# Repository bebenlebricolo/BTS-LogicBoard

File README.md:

# BTS-LogicBoard
Beer thermoregulation system logic board.
This board is meant to provide a PWM control signal to the [BTS-MainBoard-Control](https://github.com/bebenlebricolo/BTS-MainBoard-Control) board and is driven by an external "enable" signal, which is a signal coming from an external pump driver (at least in the first revisions).

This board is envisioned as a starting point as it only embeds generic electronic devices, meaning no code at all.
I've done this on purpose, to keep things relatively simple and eliminating the need to iterate over software revisions, bug fixes, etc.
As the functionalities implemented by this board are relatively simple, I thought it would be a nice alternative to go only with a NE555 (the famous one) and few other electronic components such as comparators and logic gates to perform the basic functions.

# Features
This boards boats the following features :
* 1 MHz (or so) PWM signal with linear (...or so) duty cycle control
* Cooling fan automatic turn on when board is enabled and turn off after a precalculated delay (around 120s) when the board is disabled
* Externaly driven : the PWM signal only starts up when an input signal is applied on the enable pins. This is meant to receive a pump driver signal in order to start up
* Mechanical interface (switches and potentiometer) with status leds
  * Power on status LED
  * PWM enabled status LED
  * PWM intensity status LED

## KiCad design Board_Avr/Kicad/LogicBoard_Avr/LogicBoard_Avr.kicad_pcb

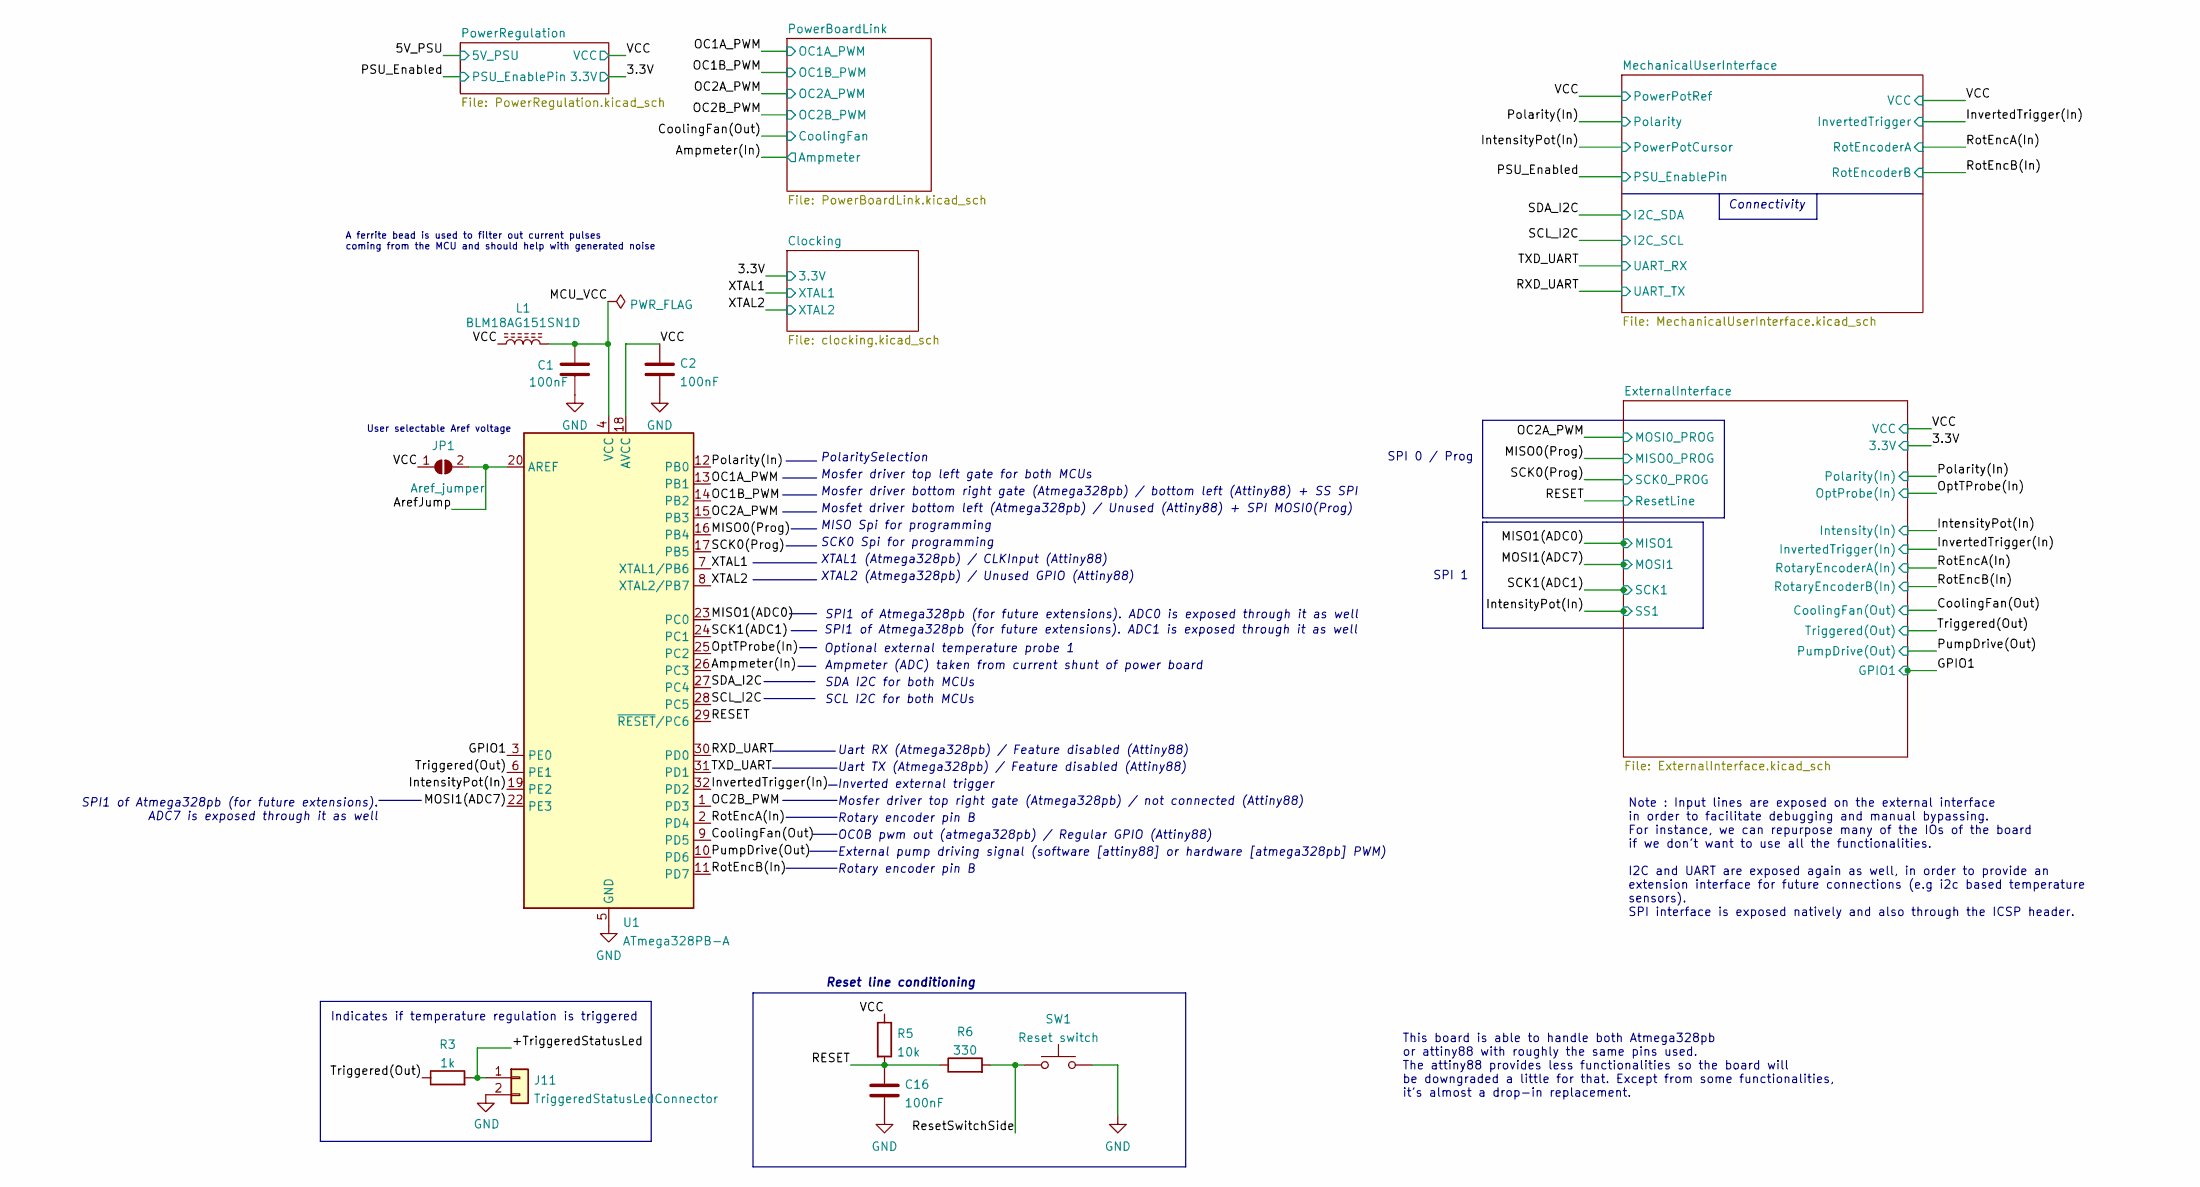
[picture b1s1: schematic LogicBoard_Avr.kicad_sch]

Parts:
C1, C2, C16: 100nF; C_1206_3216Metric
J11: TriggeredStatusLedConnector; PinHeader_1x02_P2.54mm_Vertical
JP1: Aref_jumper; SolderJumper-2_P1.3mm_Open_RoundedPad1.0x1.5mm
L1: BLM18AG151SN1D; L_0603_1608Metric
R3: 1k; R_1206_3216Metric_Pad1.30x1.75mm_HandSolder
R5: 10k; R_1206_3216Metric_Pad1.30x1.75mm_HandSolder
R6: 330; R_1206_3216Metric_Pad1.30x1.75mm_HandSolder
SW1: Reset switch; SW_PUSH_6mm_H4.3mm
U1: ATmega328PB-A; TQFP-32_7x7mm_P0.8mm

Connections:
/+TriggeredStatusLed: J11.1, R3.2
/Ampmeter(In): U1.26 (PC3); also elsewhere on the board
/ArefJump: JP1.2 (B), U1.20 (AREF)
/CoolingFan(Out): U1.9 (PD5); also elsewhere on the board
/GPIO1: U1.3 (PE0); also elsewhere on the board
/IntensityPot(In): U1.19 (PE2); also elsewhere on the board
/InvertedTrigger(In): U1.32 (PD2); also elsewhere on the board
/MCU_VCC: C1.1, L1.2, U1.4 (VCC)
/MISO0(Prog): U1.16 (PB4); also elsewhere on the board
/MISO1(ADC0): U1.23 (PC0); also elsewhere on the board
/MOSI1(ADC7): U1.22 (PE3); also elsewhere on the board
/OC1A_PWM: U1.13 (PB1); also elsewhere on the board
/OC1B_PWM: U1.14 (PB2); also elsewhere on the board
/OC2A_PWM: U1.15 (PB3); also elsewhere on the board
/OC2B_PWM: U1.1 (PD3); also elsewhere on the board
/OptTProbe(In): U1.25 (PC2); also elsewhere on the board
/Polarity(In): U1.12 (PB0); also elsewhere on the board
/PumpDrive(Out): U1.10 (PD6); also elsewhere on the board
/RESET: C16.1, R5.2, R6.1, U1.29 (~RESET/PC6); also elsewhere on the board
/RXD_UART: U1.30 (PD0); also elsewhere on the board
/ResetSwitchSide: R6.2, SW1.1
/RotEncA(In): U1.2 (PD4); also elsewhere on the board
/RotEncB(In): U1.11 (PD7); also elsewhere on the board
/SCK0(Prog): U1.17 (PB5); also elsewhere on the board
/SCK1(ADC1): U1.24 (PC1); also elsewhere on the board
/SCL_I2C: U1.28 (PC5); also elsewhere on the board
/SDA_I2C: U1.27 (PC4); also elsewhere on the board
/TXD_UART: U1.31 (PD1); also elsewhere on the board
/Triggered(Out): R3.1, U1.6 (PE1); also elsewhere on the board
/VCC: C2.1, JP1.1 (A), L1.1, R5.1, U1.18 (AVCC); also elsewhere on the board
/XTAL1: U1.7 (XTAL1/PB6); also elsewhere on the board
/XTAL2: U1.8 (XTAL2/PB7)
GND: C1.2, C2.2, C16.2, J11.2, SW1.2, U1.5 (GND), U1.21 (GND); also elsewhere on the board

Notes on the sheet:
SPI1 of Atmega328pb (for future extensions). ADC7 is exposed through it as well
Rotary encoder pin B
PolaritySelection
User selectable Aref voltage
OC0B pwm out (atmega328pb) / Regular GPIO (Attiny88)
Note : Input lines are exposed on the external interface in order to facilitate debugging and manual bypassing. For instance, we can repurpose many of the IOs of the board if we don't want to use all the functionalities. I2C and UART are exposed again as well, in order to provide an extension inter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
SPI 1
SPI1 of Atmega328pb (for future extensions). ADC1 is exposed through it as well
This board is able to handle both Atmega328pb or attiny88 with roughly the same pins used. The attiny88 provides less functionalities so the board will be downgraded a little for that. Except from some functionalities, it's almost a drop-in replacement.
XTAL2 (Atmega328pb) / Unused GPIO (Attiny88)
Mosfet driver bottom left (Atmega328pb) / Unused (Attiny88) + SPI MOSI0(Prog)
Reset line conditioning
SPI1 of Atmega328pb (for future extensions). ADC0 is exposed through it as well
Inverted external trigger
Connectivity
SDA I2C for both MCUs
MISO Spi for programming
External pump driving signal (software [attiny88] or hardware [atmega328pb] PWM)
Uart TX (Atmega328pb) / Feature disabled (Attiny88)
Mosfer driver bottom right gate (Atmega328pb) / bottom left (Attiny88) + SS SPI
Mosfer driver top left gate for both MCUs
Mosfer driver top right gate (Atmega328pb) / not connected (Attiny88)
XTAL1 (Atmega328pb) / CLKInput (Attiny88)
Ampmeter (ADC) taken from current shunt of power board
SCK0 Spi for programming
Optional external temperature probe 1
Indicates if temperature regulation is triggered
SPI 0 / Prog
Uart RX (Atmega328pb) / Feature disabled (Attiny88)
SCL I2C for both MCUs
A ferrite bead is used to filter out current pulses coming from the MCU and should help with generated noise

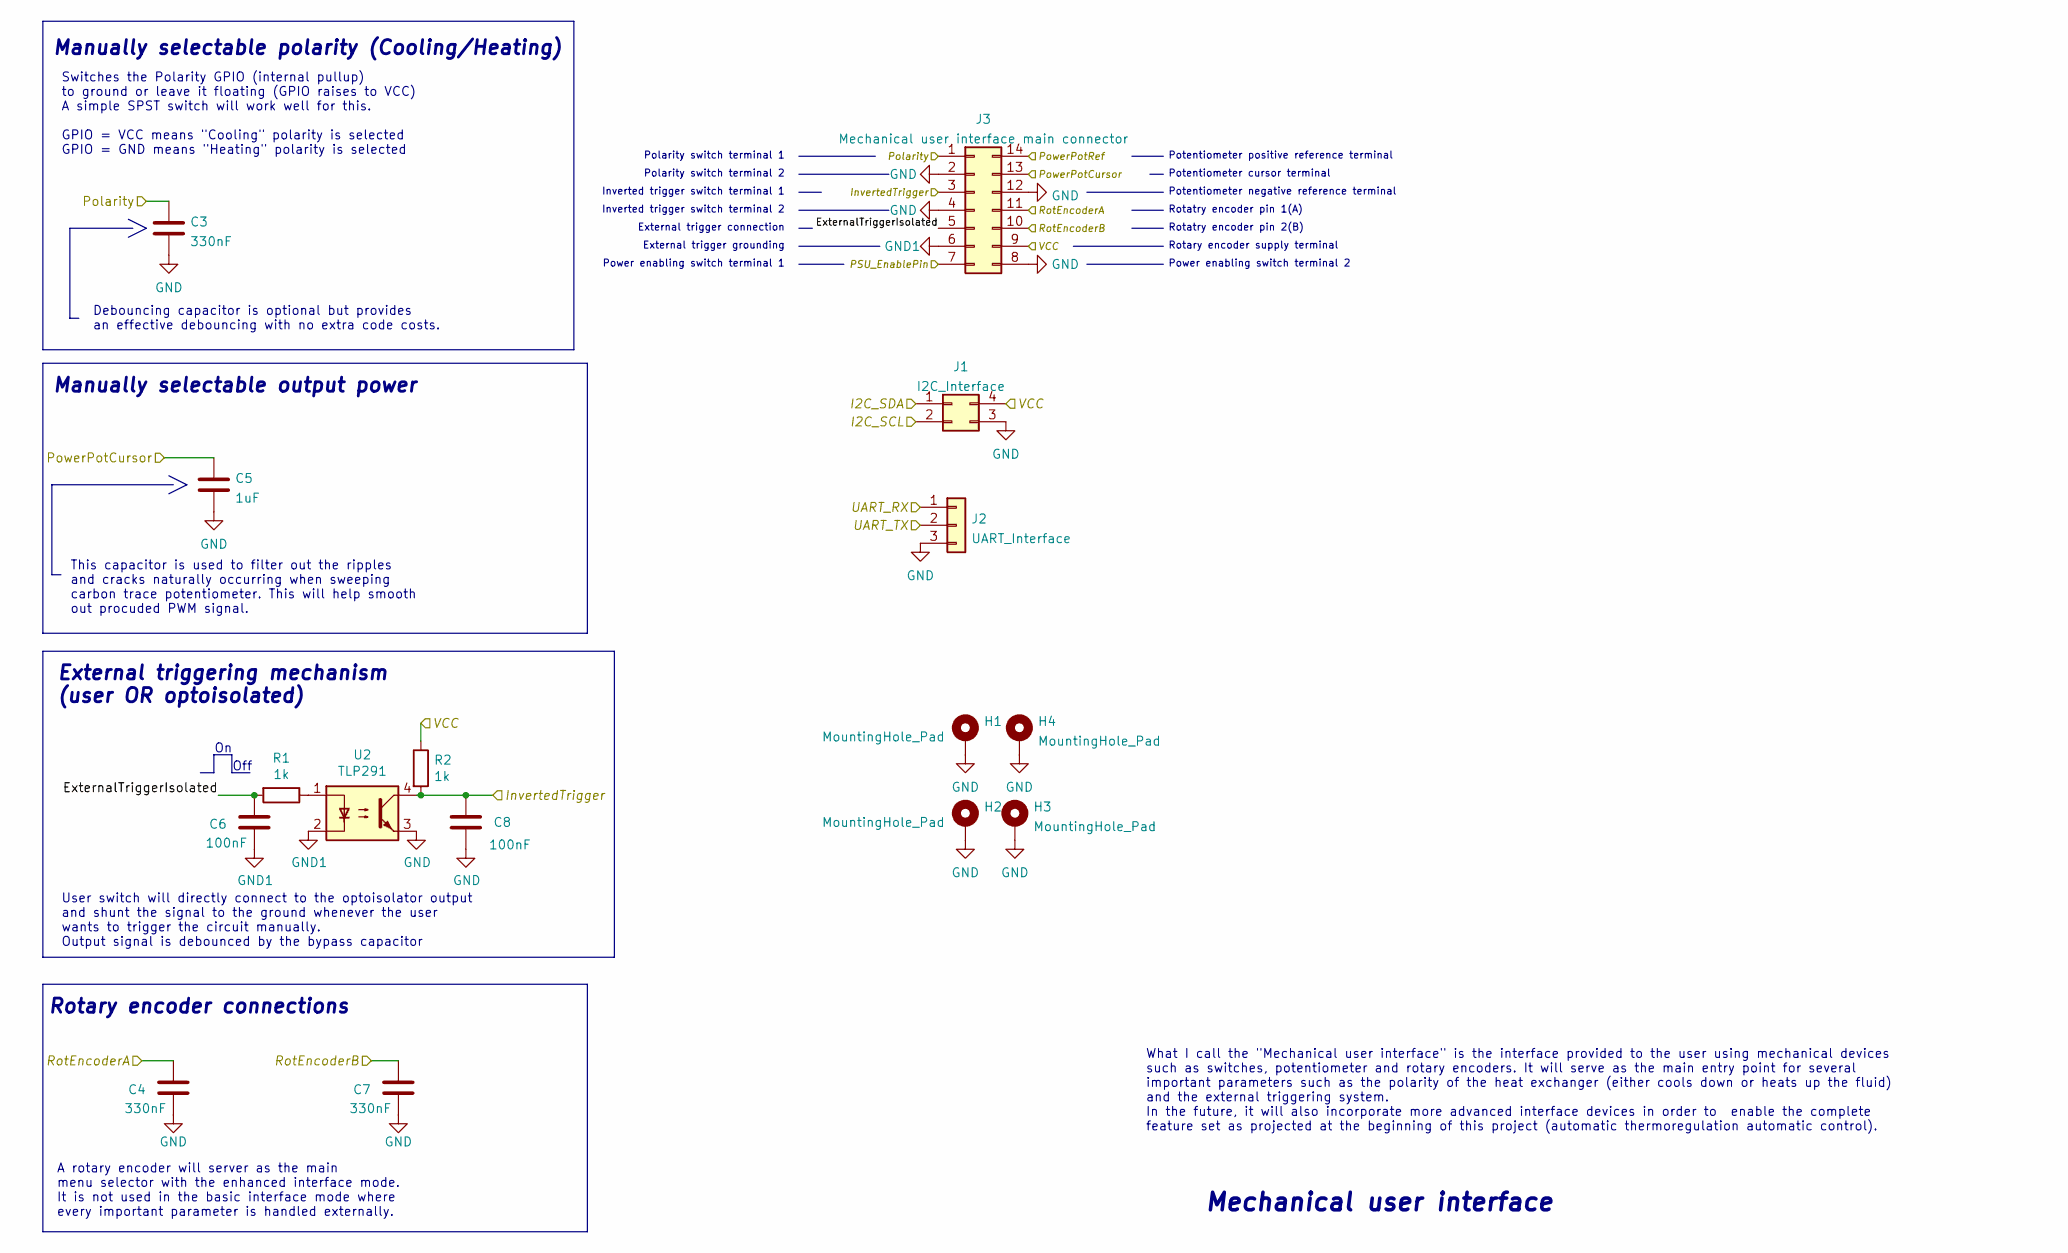
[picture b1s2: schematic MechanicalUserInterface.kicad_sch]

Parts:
C3, C4, C7: 330nF; C_1206_3216Metric
C5: 1uF; C_1206_3216Metric
C6, C8: 100nF; C_1206_3216Metric
H1, H2, H3, H4: MountingHole_Pad; MountingHole_2.5mm_Pad_Via
J1: I2C_Interface; PinHeader_2x02_P2.54mm_Vertical
J2: UART_Interface; PinHeader_1x03_P2.54mm_Vertical
J3: Mechanical user interface main connector; PinHeader_2x07_P2.54mm_Vertical
R1, R2: 1k; R_1206_3216Metric_Pad1.30x1.75mm_HandSolder
U2: TLP291; SOIC-4_4.55x2.6mm_P1.27mm

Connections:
/IntensityPot(In): C5.1, J3.13; also elsewhere on the board
/InvertedTrigger(In): C8.2, J3.3, R2.2, U2.4; also elsewhere on the board
/MechanicalUserInterface/ExternalTriggerIsolated: C6.2, J3.5, R1.2
/PSU_Enabled: J3.7; also elsewhere on the board
/Polarity(In): C3.1, J3.1; also elsewhere on the board
/RXD_UART: J2.2; also elsewhere on the board
/RotEncA(In): C4.2, J3.11; also elsewhere on the board
/RotEncB(In): C7.2, J3.10; also elsewhere on the board
/SCL_I2C: J1.2; also elsewhere on the board
/SDA_I2C: J1.1; also elsewhere on the board
/TXD_UART: J2.1; also elsewhere on the board
/VCC: J1.4, J3.9, J3.14, R2.1; also elsewhere on the board
GND: C3.2, C4.1, C5.2, C7.1, C8.1, H1.1, H2.1, H3.1, H4.1, J1.3, J2.3, J3.2, J3.4, J3.8, J3.12, U2.3; also elsewhere on the board
GND1: C6.1, J3.6, U2.2
unnamed: R1.1, U2.1

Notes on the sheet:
Rotatry encoder pin 2(B)
Rotatry encoder pin 1(A)
External triggering mechanism (user OR optoisolated)
A rotary encoder will server as the main menu selector with the enhanced interface mode. It is not used in the basic interface mode where every important parameter is handled externally.
Manually selectable polarity (Cooling/Heating)
Inverted trigger switch terminal 1
Polarity switch terminal 2
What I call the "Mechanical user interface" is the interface provided to the user using mechanical devices such as switches, potentiometer and rotary encoders. It will serve as the main entry point for several important parameters such as the polarity of the heat exchanger (either cools down or hea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
Debouncing capacitor is optional but provides an effective debouncing with no extra code costs.
External trigger grounding
Polarity switch terminal 1
Manually selectable output power
Off
User switch will directly connect to the optoisolator output and shunt the signal to the ground whenever the user wants to trigger the circuit manually. Output signal is debounced by the bypass capacitor
Switches the Polarity GPIO (internal pullup) to ground or leave it floating (GPIO raises to VCC) A simple SPST switch will work well for this. GPIO = VCC means "Cooling" polarity is selected GPIO = GND means "Heating" polarity is selected
Potentiometer cursor terminal
Potentiometer positive reference terminal
Potentiometer negative reference terminal
Mechanical user interface
Power enabling switch terminal 1
External trigger connection
Inverted trigger switch terminal 2
Rotary encoder supply terminal
This capacitor is used to filter out the ripples and cracks naturally occurring when sweeping carbon trace potentiometer. This will help smooth out procuded PWM signal.
Rotary encoder connections
Power enabling switch terminal 2

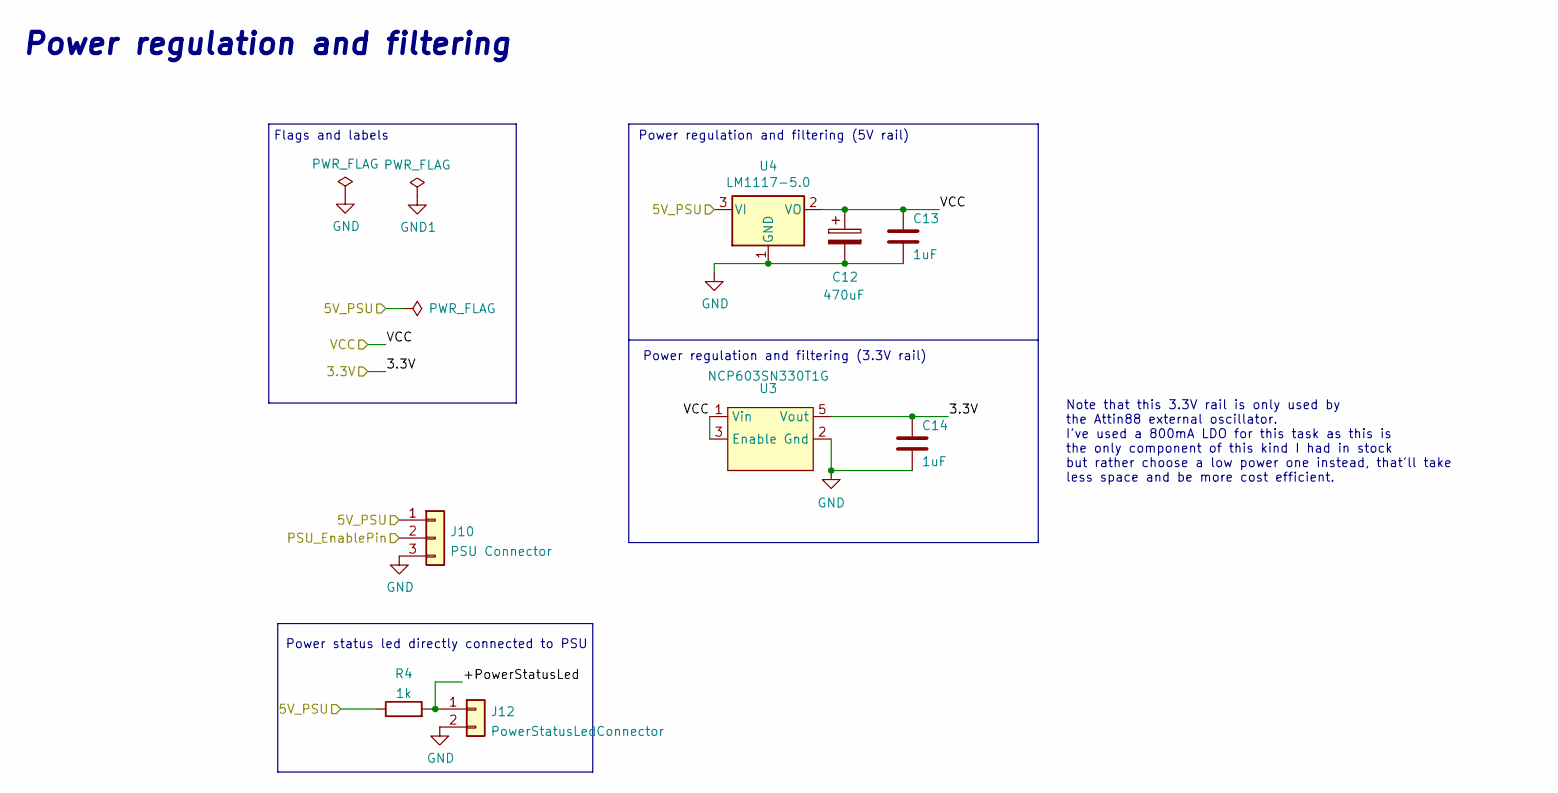
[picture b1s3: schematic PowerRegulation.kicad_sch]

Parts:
C12: 470uF; C_Elec_8x6.2
C13, C14: 1uF; C_1206_3216Metric
J10: PSU Connector; 559350310
J12: PowerStatusLedConnector; PinHeader_1x02_P2.54mm_Vertical
R4: 1k; R_1206_3216Metric_Pad1.30x1.75mm_HandSolder
U3: NCP603SN330T1G; TSOP-5_1.65x3.05mm_P0.95mm
U4: LM1117-5.0; SOT-223-3_TabPin2

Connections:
/3.3V: C14.1, U3.5 (Vout); also elsewhere on the board
/5V_PSU: J10.1, R4.1, U4.3 (VI)
/PSU_Enabled: J10.2; also elsewhere on the board
/PowerRegulation/+PowerStatusLed: J12.1, R4.2
/VCC: C12.1, C13.1, U3.1 (Vin), U3.3 (Enable), U4.2 (VO); also elsewhere on the board
GND: C12.2, C13.2, C14.2, J10.3, J12.2, U3.2 (Gnd), U4.1 (GND); also elsewhere on the board

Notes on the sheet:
Note that this 3.3V rail is only used by the Attin88 external oscillator. I've used a 800mA LDO for this task as this is the only component of this kind I had in stock but rather choose a low power one instead, that'll take less space and be more cost efficient.
Power regulation and filtering (5V rail)
Power regulation and filtering (3.3V rail)
Power status led directly connected to PSU
Power regulation and filtering
Flags and labels

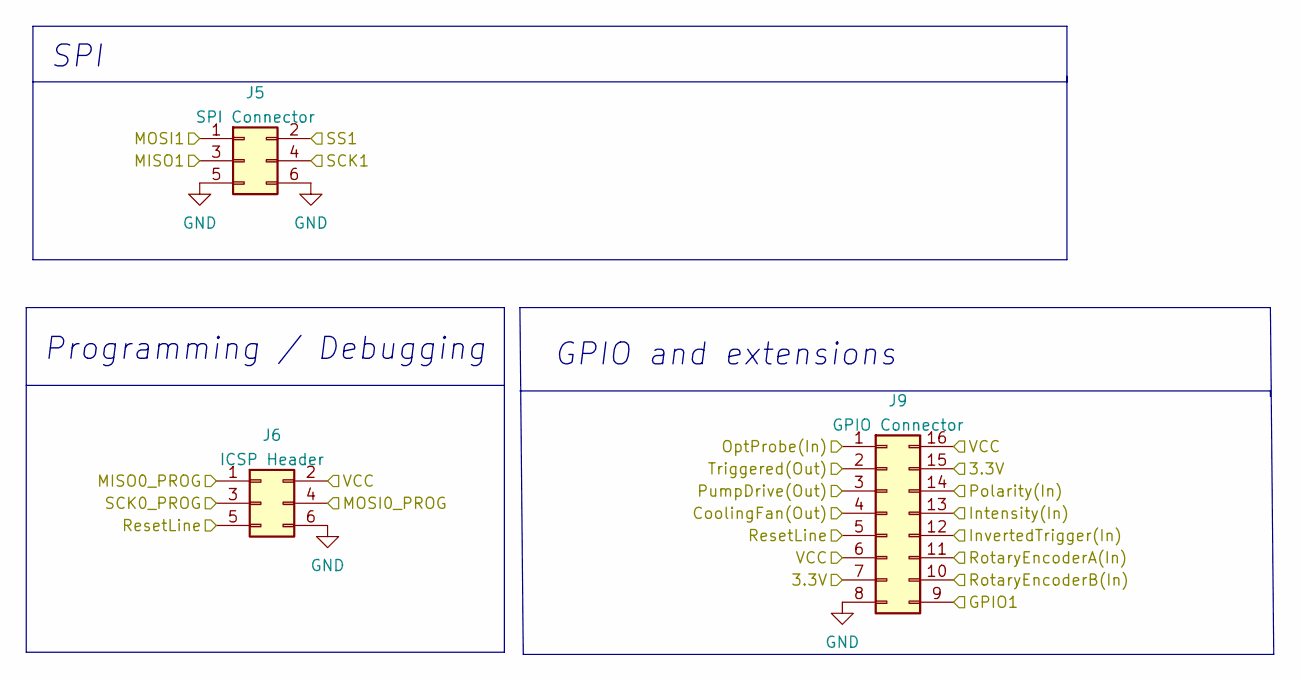
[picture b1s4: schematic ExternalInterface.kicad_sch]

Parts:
J5: SPI Connector; PinHeader_2x03_P2.54mm_Vertical
J6: ICSP Header; PinHeader_2x03_P2.54mm_Vertical
J9: GPIO Connector; PinHeader_2x08_P2.54mm_Vertical

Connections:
/3.3V: J9.7, J9.15; also elsewhere on the board
/CoolingFan(Out): J9.4; also elsewhere on the board
/GPIO1: J9.9; also elsewhere on the board
/IntensityPot(In): J5.2, J9.13; also elsewhere on the board
/InvertedTrigger(In): J9.12; also elsewhere on the board
/MISO0(Prog): J6.1; also elsewhere on the board
/MISO1(ADC0): J5.3; also elsewhere on the board
/MOSI1(ADC7): J5.1; also elsewhere on the board
/OC2A_PWM: J6.4; also elsewhere on the board
/OptTProbe(In): J9.1; also elsewhere on the board
/Polarity(In): J9.14; also elsewhere on the board
/PumpDrive(Out): J9.3; also elsewhere on the board
/RESET: J6.5, J9.5; also elsewhere on the board
/RotEncA(In): J9.11; also elsewhere on the board
/RotEncB(In): J9.10; also elsewhere on the board
/SCK0(Prog): J6.3; also elsewhere on the board
/SCK1(ADC1): J5.4; also elsewhere on the board
/Triggered(Out): J9.2; also elsewhere on the board
/VCC: J6.2, J9.6, J9.16; also elsewhere on the board
GND: J5.5, J5.6, J6.6, J9.8; also elsewhere on the board

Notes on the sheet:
GPIO and extensions
SPI
Programming / Debugging

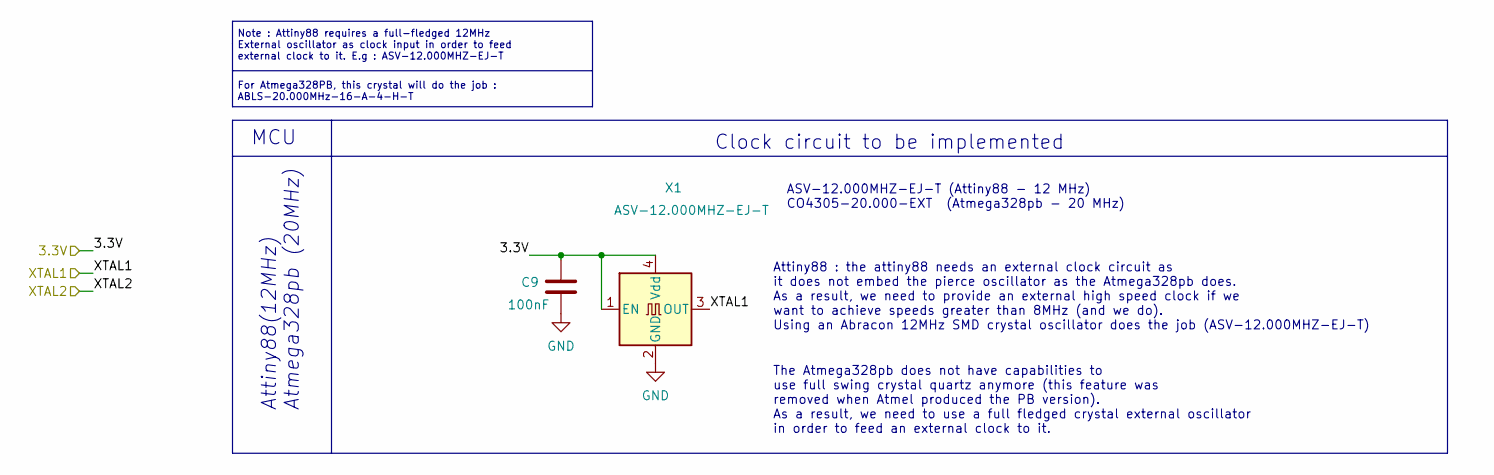
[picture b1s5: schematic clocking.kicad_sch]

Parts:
C9: 100nF; C_1206_3216Metric
X1: ASV-12.000MHZ-EJ-T; Oscillator_SMD_Abracon_ASV-4Pin_7.0x5.1mm

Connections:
/3.3V: C9.1, X1.1 (EN), X1.4 (Vdd); also elsewhere on the board
/XTAL1: X1.3 (OUT); also elsewhere on the board
GND: C9.2, X1.2 (GND); also elsewhere on the board

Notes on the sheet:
Attiny88(12MHz) Atmega328pb (20MHz)
For Atmega328PB, this crystal will do the job : ABLS-20.000MHz-16-A-4-H-T
Attiny88 : the attiny88 needs an external clock circuit as it does not embed the pierce oscillator as the Atmega328pb does. As a result, we need to provide an external high speed clock if we want to achieve speeds greater than 8MHz (and we do). Using an Abracon 12MHz SMD crystal oscillator does the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
MCU
ASV-12.000MHZ-EJ-T (Attiny88 - 12 MHz) CO4305-20.000-EXT (Atmega328pb - 20 MHz)
Clock circuit to be implemented
Note : Attiny88 requires a full-fledged 12MHz External oscillator as clock input in order to feed external clock to it. E.g : ASV-12.000MHZ-EJ-T
The Atmega328pb does not have capabilities to use full swing crystal quartz anymore (this feature was removed when Atmel produced the PB version). As a result, we need to use a full fledged crystal external oscillator in order to feed an external clock to it.

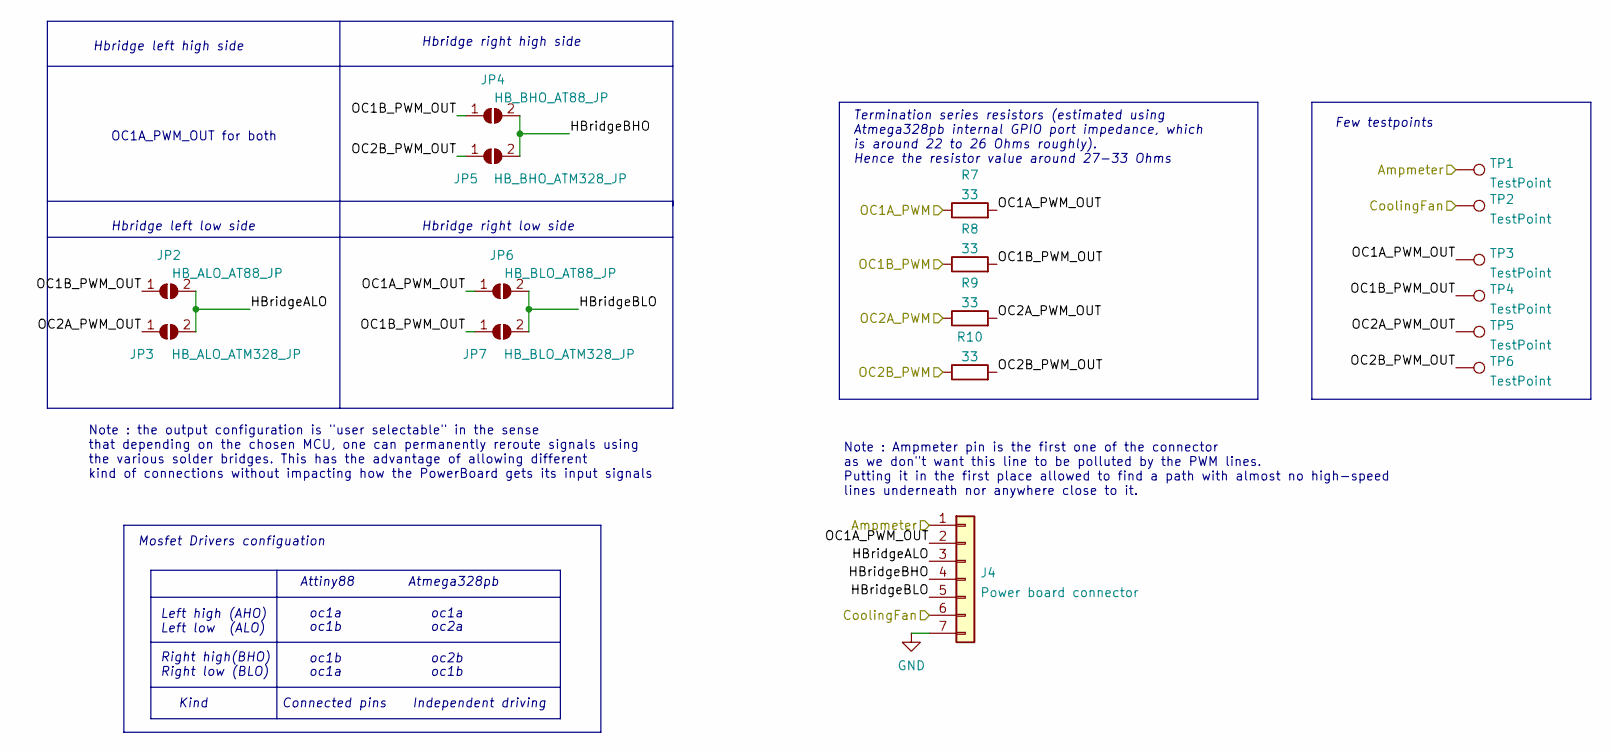
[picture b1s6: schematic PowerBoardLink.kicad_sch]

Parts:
J4: Power board connector; PinHeader_1x07_P2.54mm_Vertical
JP2: HB_ALO_AT88_JP; SolderJumper-2_P1.3mm_Open_RoundedPad1.0x1.5mm
JP3: HB_ALO_ATM328_JP; SolderJumper-2_P1.3mm_Open_RoundedPad1.0x1.5mm
JP4: HB_BHO_AT88_JP; SolderJumper-2_P1.3mm_Open_RoundedPad1.0x1.5mm
JP5: HB_BHO_ATM328_JP; SolderJumper-2_P1.3mm_Open_RoundedPad1.0x1.5mm
JP6: HB_BLO_AT88_JP; SolderJumper-2_P1.3mm_Open_RoundedPad1.0x1.5mm
JP7: HB_BLO_ATM328_JP; SolderJumper-2_P1.3mm_Open_RoundedPad1.0x1.5mm
R7, R8, R9, R10: 33; R_0402_1005Metric_Pad0.72x0.64mm_HandSolder
TP1, TP2, TP3, TP4, TP5, TP6: TestPoint; TestPoint_Pad_D1.0mm

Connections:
/Ampmeter(In): J4.1, TP1.1; also elsewhere on the board
/CoolingFan(Out): J4.6, TP2.1; also elsewhere on the board
/OC1A_PWM: R7.1; also elsewhere on the board
/OC1B_PWM: R8.1; also elsewhere on the board
/OC2A_PWM: R9.1; also elsewhere on the board
/OC2B_PWM: R10.1; also elsewhere on the board
/PowerBoardLink/HBridgeALO: J4.3, JP2.2 (B), JP3.2 (B)
/PowerBoardLink/HBridgeBHO: J4.4, JP4.2 (B), JP5.2 (B)
/PowerBoardLink/HBridgeBLO: J4.5, JP6.2 (B), JP7.2 (B)
/PowerBoardLink/OC1A_PWM_OUT: J4.2, JP6.1 (A), R7.2, TP3.1
/PowerBoardLink/OC1B_PWM_OUT: JP2.1 (A), JP4.1 (A), JP7.1 (A), R8.2, TP4.1
/PowerBoardLink/OC2A_PWM_OUT: JP3.1 (A), R9.2, TP5.1
/PowerBoardLink/OC2B_PWM_OUT: JP5.1 (A), R10.2, TP6.1
GND: J4.7; also elsewhere on the board

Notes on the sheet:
Note : the output configuration is "user selectable" in the sense that depending on the chosen MCU, one can permanently reroute signals using the various solder bridges. This has the advantage of allowing different kind of connections without impacting how the PowerBoard gets its input signals
Kind
Connected pins
Hbridge right high side
Hbridge right low side
Hbridge left high side
Mosfet Drivers configuation
Left high (AHO) Left low (ALO) Right high(BHO) Right low (BLO)
oc2a
Few testpoints
oc1b
Atmega328pb
Note : Ampmeter pin is the first one of the connector as we don"t want this line to be polluted by the PWM lines. Putting it in the first place allowed to find a path with almost no high-speed lines underneath nor anywhere close to it.
Termination series resistors (estimated using Atmega328pb internal GPIO port impedance, which is around 22 to 26 Ohms roughly). Hence the resistor value around 27-33 Ohms
oc1a
Attiny88
Independent driving
OC1A_PWM_OUT for both
oc2b
Hbridge left low side

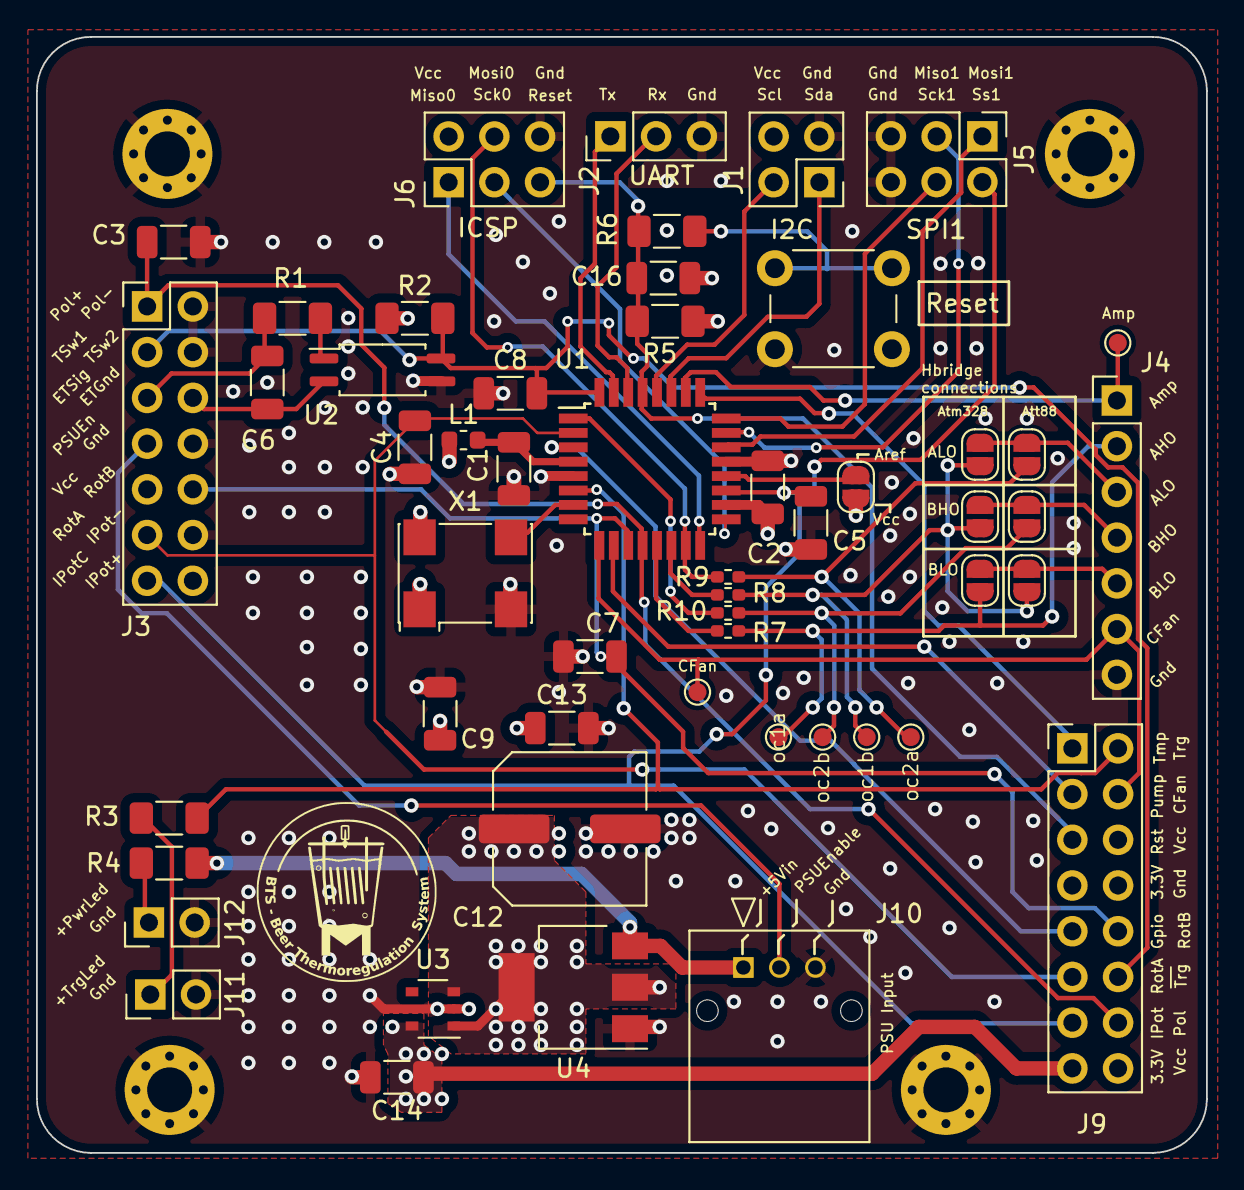
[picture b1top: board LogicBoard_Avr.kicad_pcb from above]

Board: 4 copper layers, 65.0 x 62.0 mm, 57 parts (0 on the bottom side), 46 nets.

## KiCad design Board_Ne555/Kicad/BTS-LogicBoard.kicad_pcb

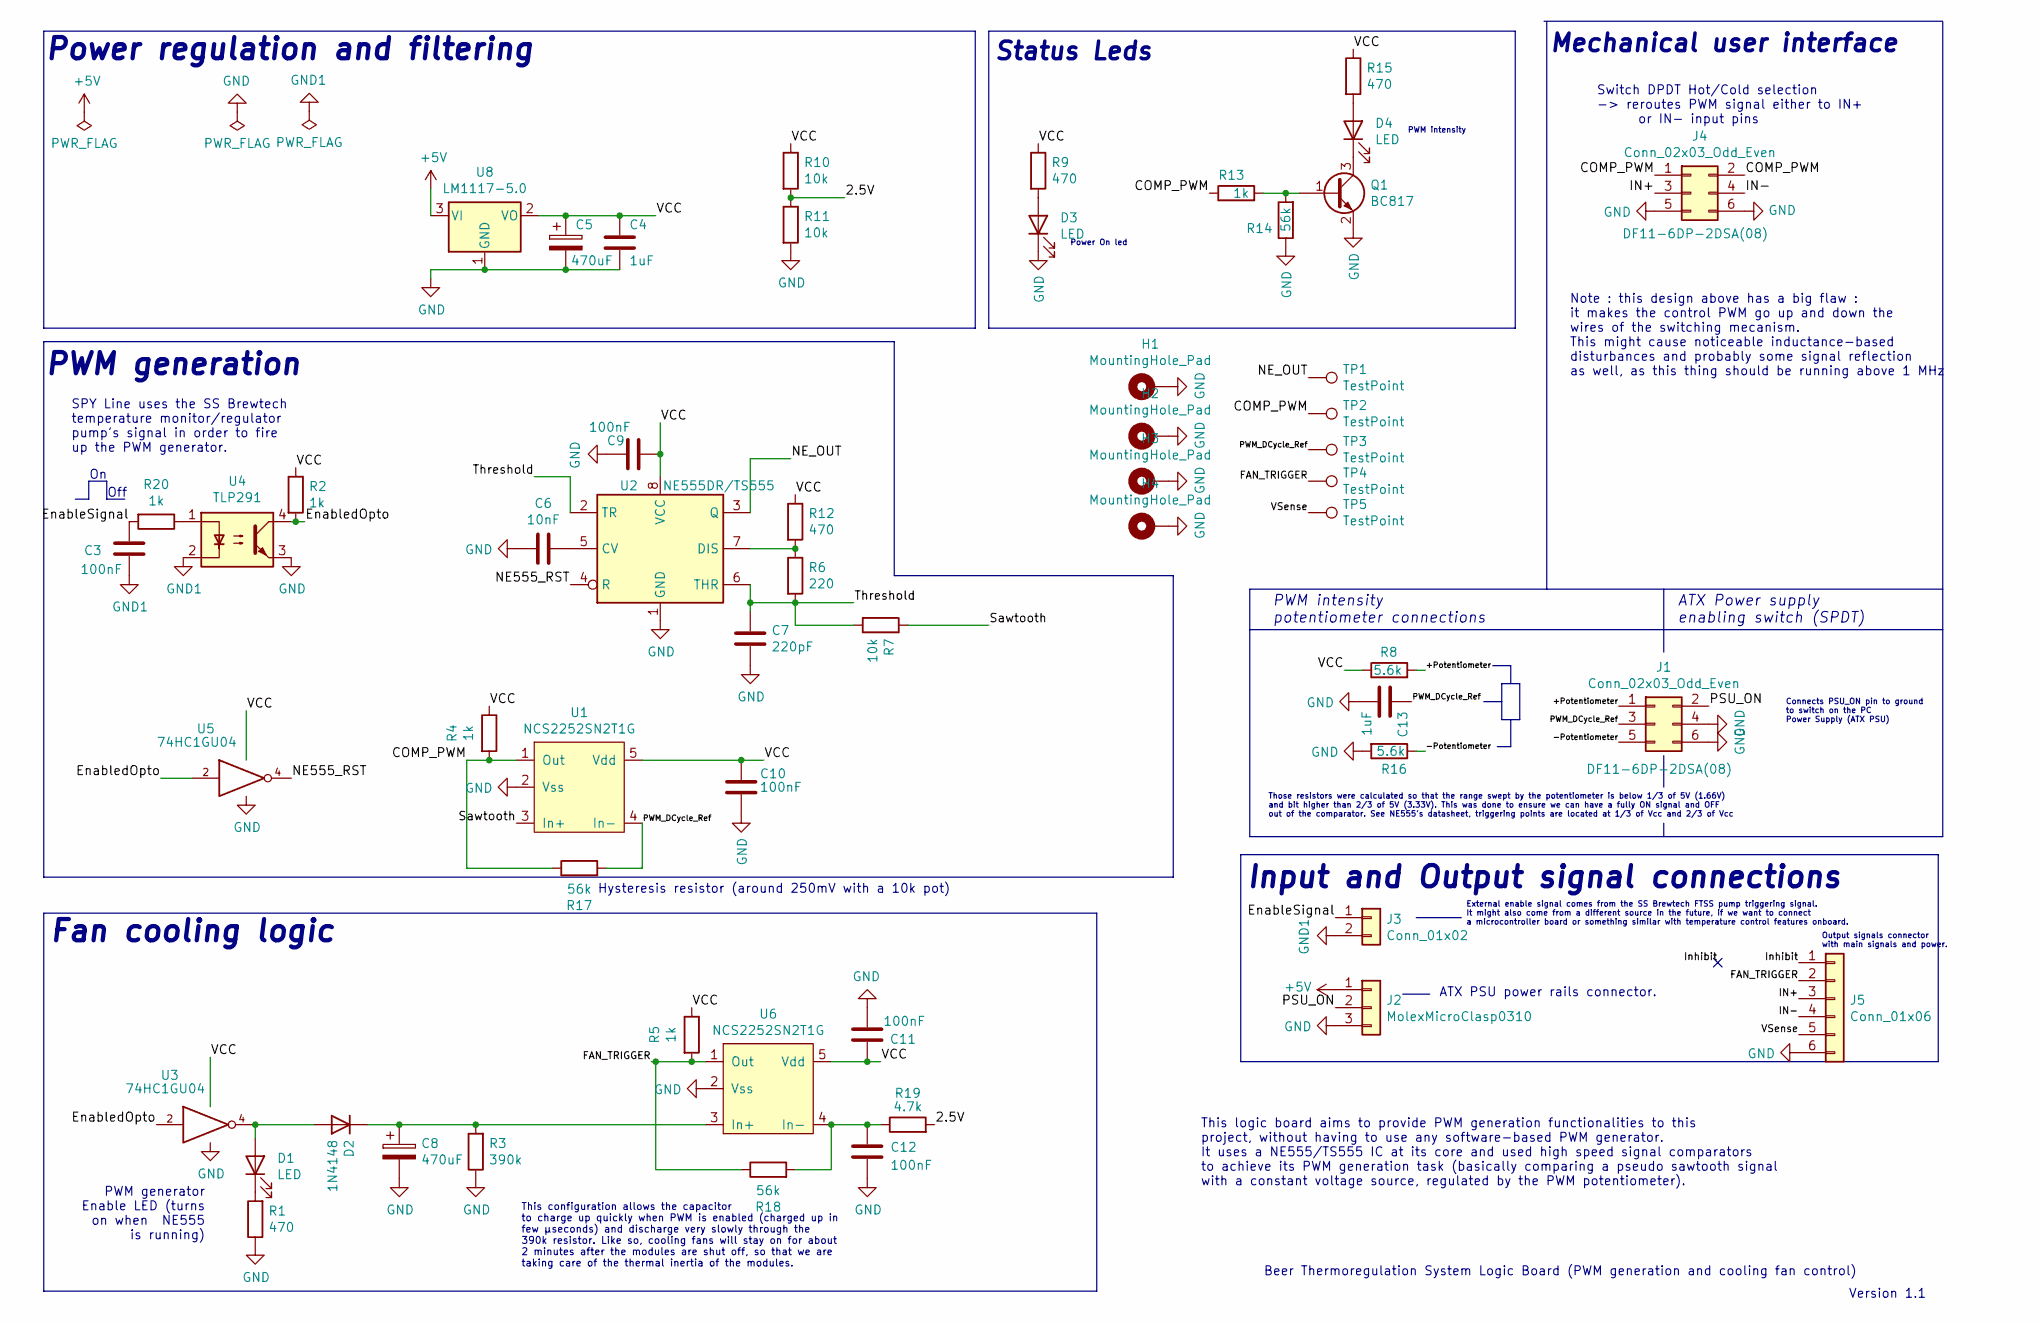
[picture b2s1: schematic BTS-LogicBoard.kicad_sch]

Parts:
C3, C9, C10, C11, C12: 100nF; C_1206_3216Metric_Pad1.33x1.80mm_HandSolder
C4, C13: 1uF; C_1206_3216Metric_Pad1.33x1.80mm_HandSolder
C5, C8: 470uF; CP_Elec_10x10
C6: 10nF; C_1206_3216Metric_Pad1.33x1.80mm_HandSolder
C7: 220pF; C_1206_3216Metric_Pad1.33x1.80mm_HandSolder
D1, D3, D4: LED; LED_D3.0mm
D2: 1N4148; D_1206_3216Metric_Pad1.42x1.75mm_HandSolder
H1, H2, H3, H4: MountingHole_Pad; MountingHole_3.2mm_M3_DIN965_Pad_TopBottom
J1, J4: Conn_02x03_Odd_Even; Hirose_DF11-6DP-2DSA_2x03_P2.00mm_Vertical; PartNumber DF11-6DP-2DSA(08)
J2: MolexMicroClasp0310; 559350310; PartNumber 55935-0310
J3: Conn_01x02; PinSocket_1x02_P2.54mm_Vertical
J5: Conn_01x06; Molex_MicroLock_1.25_01x06
Q1: BC817; SOT-23
R1, R9, R12, R15: 470; R_1206_3216Metric_Pad1.30x1.75mm_HandSolder
R2, R4, R5, R13, R20: 1k; R_1206_3216Metric_Pad1.30x1.75mm_HandSolder
R3: 390k; R_1206_3216Metric_Pad1.30x1.75mm_HandSolder
R6: 220; R_1206_3216Metric_Pad1.30x1.75mm_HandSolder
R7, R10, R11: 10k; R_1206_3216Metric_Pad1.30x1.75mm_HandSolder
R8, R16: 5.6k; R_1206_3216Metric_Pad1.30x1.75mm_HandSolder
R14, R17, R18: 56k; R_1206_3216Metric_Pad1.30x1.75mm_HandSolder
R19: 4.7k; R_1206_3216Metric_Pad1.30x1.75mm_HandSolder
TP1, TP2, TP3, TP4, TP5: TestPoint; TestPoint_Pad_D2.0mm
U1, U6: NCS2252SN2T1G; SOT-23-5
U2: NE555DR/TS555; SOIC-8_3.9x4.9mm_P1.27mm
U3, U5: 74HC1GU04; SOT-353_SC-70-5
U4: TLP291; SOIC-4_4.55x2.6mm_P1.27mm
U8: LM1117-5.0; SOT-223-3_TabPin2

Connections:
+5V: J2.1, U8.3 (VI)
/2.5V: R10.2, R11.1, R19.2
/+Potentiometer: J1.1, R8.2
/-Potentiometer: J1.5, R16.1
/COMP_PWM: J4.1, J4.2, R4.2, R13.1, R17.1, TP2.1, U1.1 (Out)
/EnableSignal: C3.2, J3.1, R20.2
/EnabledOpto: R2.2, U3.2, U4.4, U5.2
/FAN_TRIGGER: J5.2, R5.2, R18.1, TP4.1, U6.1 (Out)
/IN+: J4.3, J5.3
/IN-: J4.4, J5.4
/NE555_RST: U2.4 (R), U5.4
/NE_OUT: TP1.1, U2.3 (Q)
/PSU_ON: J1.2, J2.2
/PWM_DCycle_Ref: C13.1, J1.3, R17.2, TP3.1, U1.4 (In-)
/Sawtooth: R7.1, U1.3 (In+)
/Threshold: C7.1, R6.2, R7.2, U2.2 (TR), U2.6 (THR)
/VSense: J5.5, TP5.1
GND: C4.2, C5.2, C6.2, C7.2, C8.2, C9.2, C10.2, C11.2, C12.2, C13.2, D3.1 (K), H1.1, H2.1, H3.1, H4.1, J1.4, J1.6, J2.3, J4.5, J4.6, J5.6, Q1.2 (E), R1.1, R3.1, R11.2, R14.1, R16.2, U1.2 (Vss), U2.1 (GND), U3.3 (GND), U4.3, U5.3 (GND), U6.2 (Vss), U8.1 (GND)
GND1: C3.1, J3.2, U4.2
unnamed: C6.1, U2.5 (CV)
unnamed: C8.1, D2.1 (K), R3.2, U6.3 (In+)
unnamed: C12.1, R18.2, R19.1, U6.4 (In-)
unnamed: D1.1 (K), R1.2
unnamed: D1.2 (A), D2.2 (A), U3.4
unnamed: D3.2 (A), R9.2
unnamed: D4.1 (K), Q1.3 (C)
unnamed: D4.2 (A), R15.2
unnamed: Q1.1 (B), R13.2, R14.2
unnamed: R6.1, R12.2, U2.7 (DIS)
unnamed: R20.1, U4.1
VCC: C4.1, C5.1, C9.1, C10.1, C11.1, R2.1, R4.1, R5.1, R8.1, R9.1, R10.1, R12.1, R15.1, U1.5 (Vdd), U2.8 (VCC), U3.5 (VCC), U5.5 (VCC), U6.5 (Vdd), U8.2 (VO)

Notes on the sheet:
Connects PSU_ON pin to ground to switch on the PC Power Supply (ATX PSU)
Output signals connector with main signals and power.
Version 1.1
Fan cooling logic
Off
Mechanical user interface
Power On led
Beer Thermoregulation System Logic Board (PWM generation and cooling fan control)
Hysteresis resistor (around 250mV with a 10k pot)
This logic board aims to provide PWM generation functionalities to this project, without having to use any software-based PWM generator. It uses a NE555/TS555 IC at its core and used high speed signal comparators to achieve its PWM generation task (basically comparing a pseudo sawtooth signal with 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
Those resistors were calculated so that the range swept by the potentiometer is below 1/3 of 5V (1.66V) and bit higher than 2/3 of 5V (3.33V). This was done to ensure we can have a fully ON signal and OFF out of the comparator. See NE555's datasheet, triggering points are located at 1/3 of Vcc and 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
Power regulation and filtering
Input and Output signal connections
Switch DPDT Hot/Cold selection -> reroutes PWM signal either to IN+ or IN- input pins
PWM generator Enable LED (turns on when NE555 is running)
External enable signal comes from the SS Brewtech FTSS pump triggering signal. It might also come from a different source in the future, if we want to connect a microcontroller board or something similar with temperature control features onboard.
This configuration allows the capacitor to charge up quickly when PWM is enabled (charged up in few µseconds) and discharge very slowly through the 390k resistor. Like so, cooling fans will stay on for about 2 minutes after the modules are shut off, so that we are taking care of the thermal inertia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
Note : this design above has a big flaw : it makes the control PWM go up and down the wires of the switching mecanism. This might cause noticeable inductance-based disturbances and probably some signal reflection as well, as this thing should be running above 1 MHz
PWM intensity potentiometer connections
ATX Power supply enabling switch (SPDT)
ATX PSU power rails connector.
SPY Line uses the SS Brewtech temperature monitor/regulator pump's signal in order to fire up the PWM generator.
Status Leds
PWM intensity
PWM generation

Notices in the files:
parts and their libraries:
Copyright 2021 Accelerated Designs. All rights reserved.
